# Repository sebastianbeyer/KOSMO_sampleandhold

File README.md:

Triple Sample and Hold module based on the [Schmitzbits YASH](https://www.schmitzbits.de/sah.html). 
I changed some values to improve the droop rate, because I want to use it to sample CV and not audio.
If nothing is plugged into the inputs, it will sample white noise (should be 6V p2p, but you might tweak 
the values of resistors because it always depends on the transistor (reverse avalanche noise)

### Videos to show drop rate with different values for the S&H capacitor

https://www.youtube.com/watch?v=smofjtYN6VY

https://www.youtube.com/watch?v=RdAyaS16wt8

https://www.youtube.com/watch?v=JDEQTLfsh5g

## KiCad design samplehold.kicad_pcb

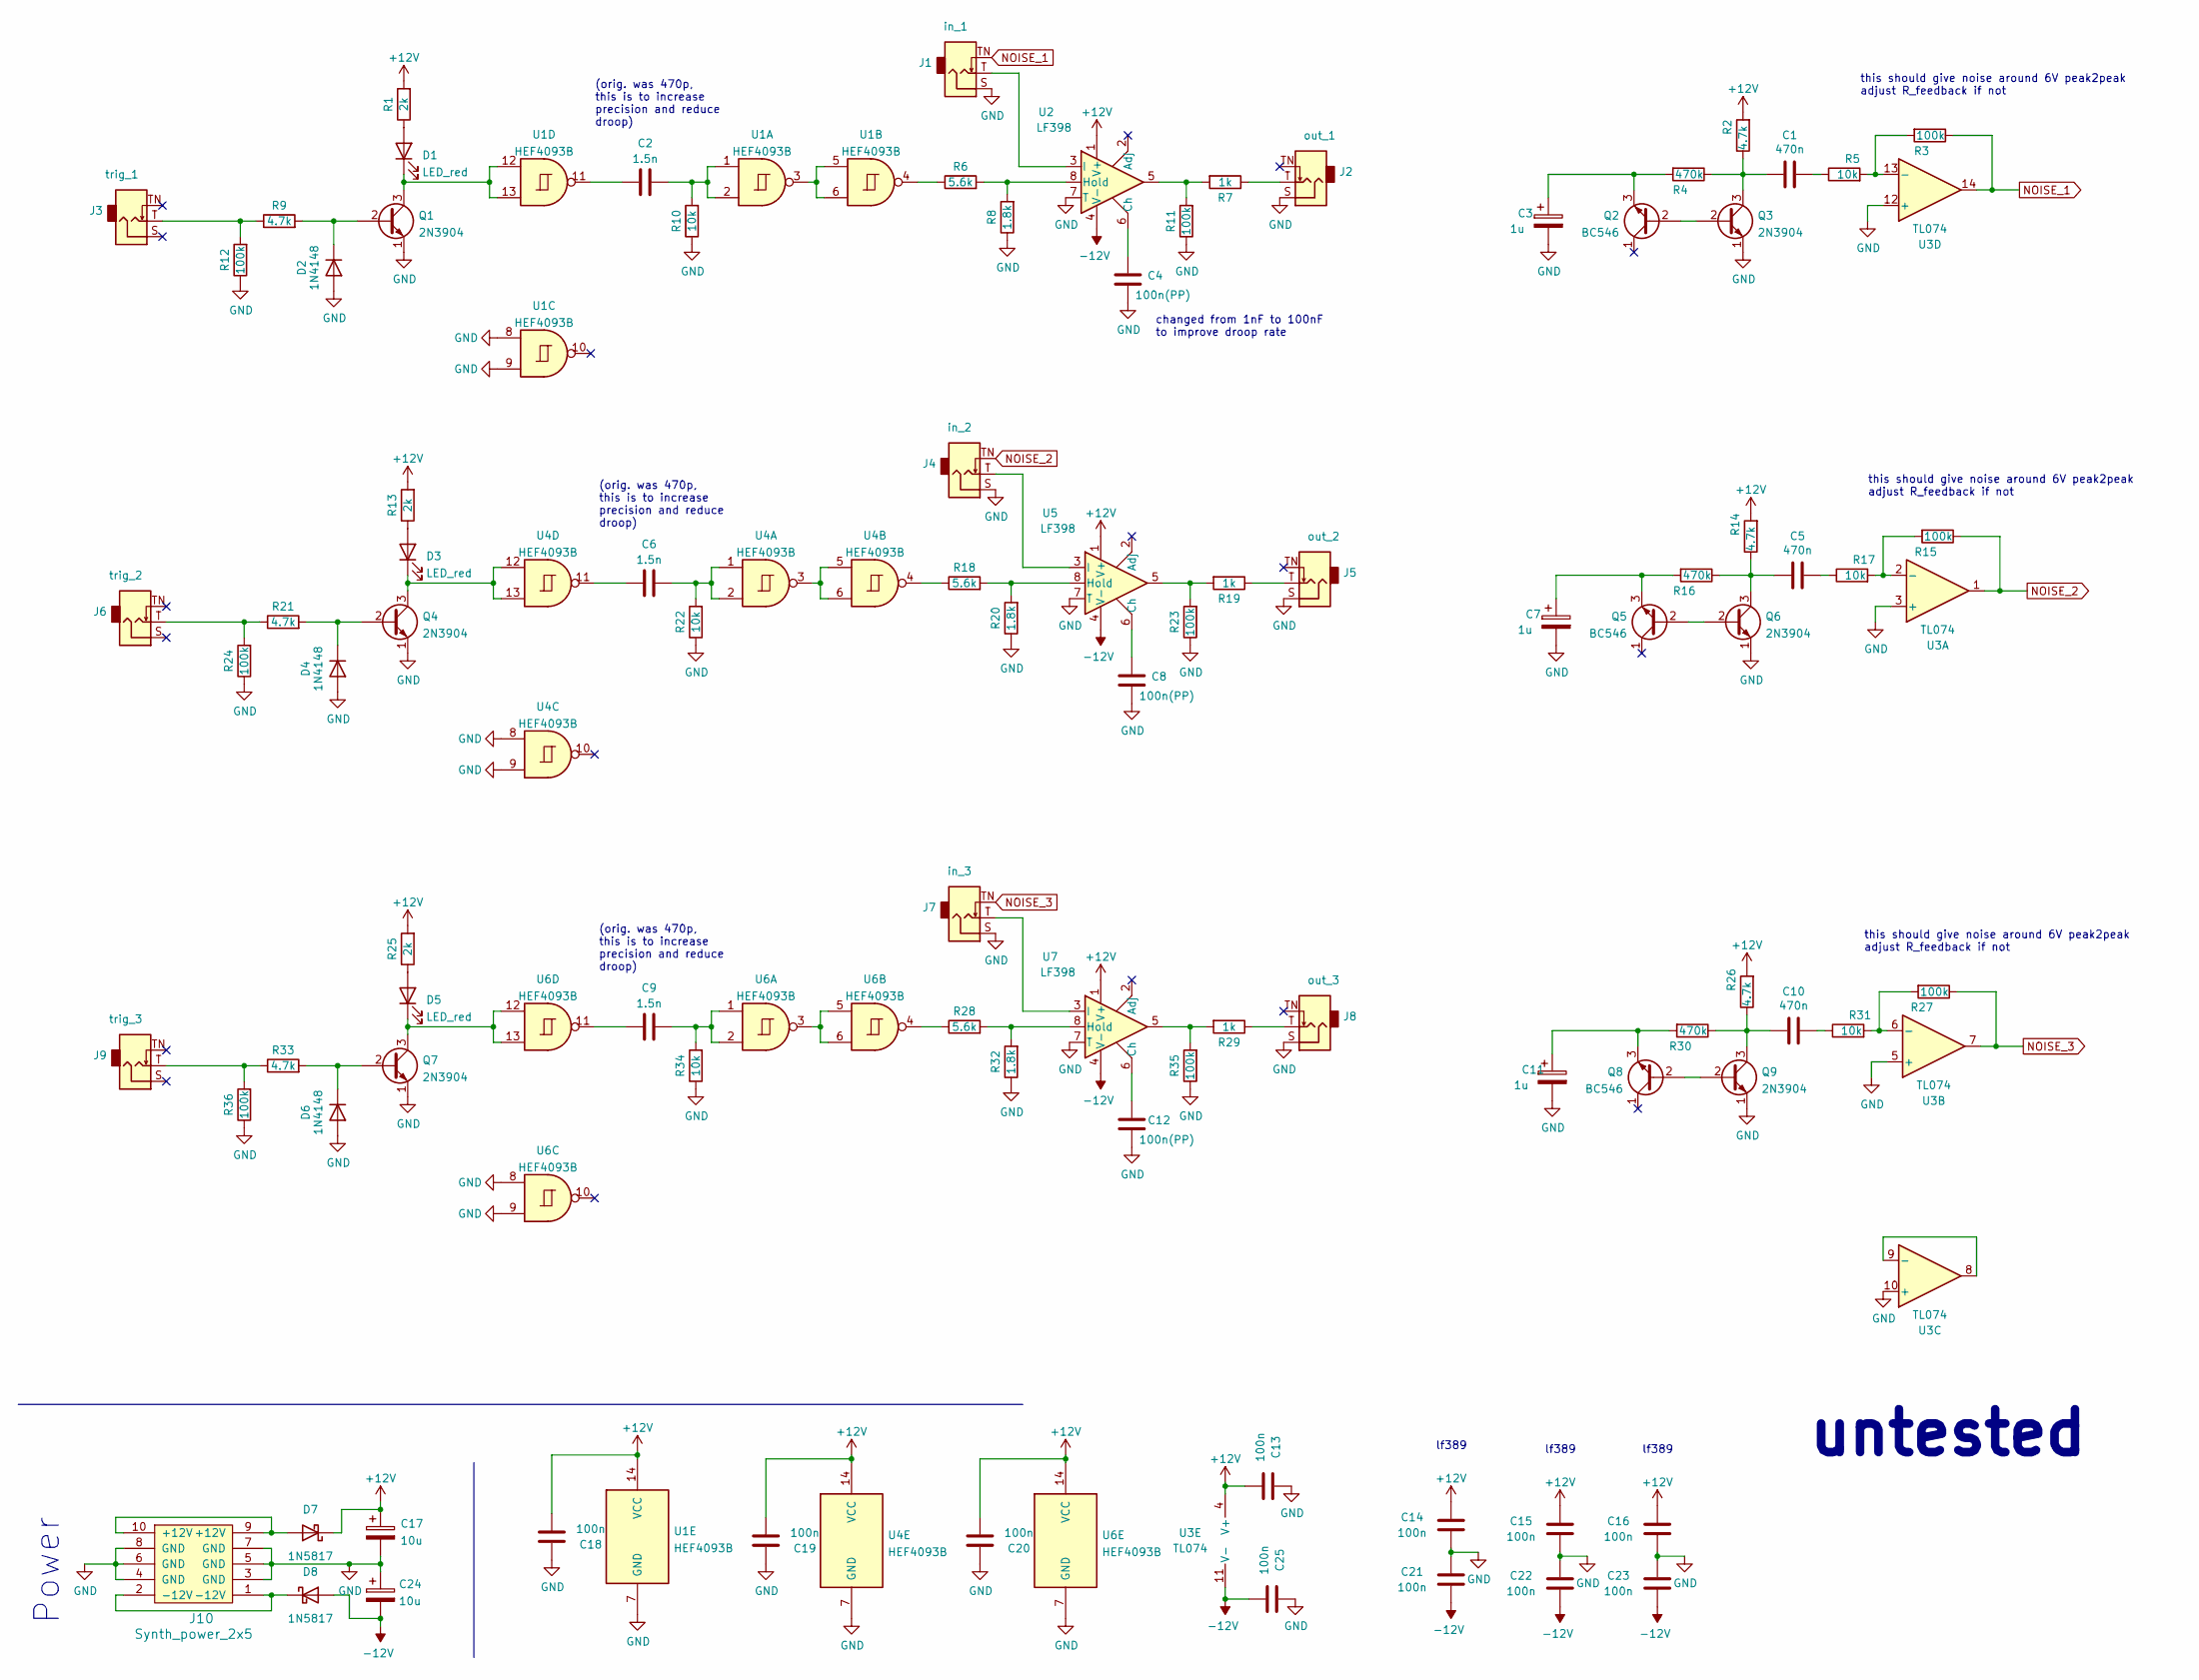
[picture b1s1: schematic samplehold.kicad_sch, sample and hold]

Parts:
C1, C5, C10: 470n; C_Rect_L7.2mm_W2.5mm_P5.00mm_FKS2_FKP2_MKS2_MKP2
C2, C6, C9: 1.5n; C_Rect_L7.2mm_W2.5mm_P5.00mm_FKS2_FKP2_MKS2_MKP2
C3, C7, C11: 1u; CP_Radial_D5.0mm_P2.00mm
C4, C8, C12: 100n(PP); C_Rect_L7.2mm_W2.5mm_P5.00mm_FKS2_FKP2_MKS2_MKP2
C13, C14, C15, C16, C18, C19, C20, C21, C22, C23, C25: 100n; C_Disc_D3.0mm_W1.6mm_P2.50mm
C17, C24: 10u; CP_Radial_D6.3mm_P2.50mm
D1, D3, D5: LED_red; LED_D5.0mm
D2, D4, D6: 1N4148; D_DO-35_SOD27_P7.62mm_Horizontal
D7, D8: 1N5817; D_DO-41_SOD81_P7.62mm_Horizontal
J1: in_1; Jack_6.35mm_PJ_629HAN
J2: out_1; Jack_6.35mm_PJ_629HAN
J3: trig_1; Jack_6.35mm_PJ_629HAN
J4: in_2; Jack_6.35mm_PJ_629HAN
J5: out_2; Jack_6.35mm_PJ_629HAN
J6: trig_2; Jack_6.35mm_PJ_629HAN
J7: in_3; Jack_6.35mm_PJ_629HAN
J8: out_3; Jack_6.35mm_PJ_629HAN
J9: trig_3; Jack_6.35mm_PJ_629HAN
J10: Synth_power_2x5; Power_Header
Q1, Q3, Q4, Q6, Q7, Q9: 2N3904; TO-92_Inline_Wide
Q2, Q5, Q8: BC546; TO-92_Inline_Wide
R1, R13, R25: 2k; R_Axial_DIN0207_L6.3mm_D2.5mm_P2.54mm_Vertical
R2, R9, R14, R21, R26, R33: 4.7k; R_Axial_DIN0207_L6.3mm_D2.5mm_P2.54mm_Vertical
R3, R11, R12, R15, R23, R24, R27, R35, R36: 100k; R_Axial_DIN0207_L6.3mm_D2.5mm_P2.54mm_Vertical
R4, R16, R30: 470k; R_Axial_DIN0207_L6.3mm_D2.5mm_P2.54mm_Vertical
R5, R10, R17, R22, R31, R34: 10k; R_Axial_DIN0207_L6.3mm_D2.5mm_P2.54mm_Vertical
R6, R18, R28: 5.6k; R_Axial_DIN0207_L6.3mm_D2.5mm_P2.54mm_Vertical
R7, R19, R29: 1k; R_Axial_DIN0207_L6.3mm_D2.5mm_P2.54mm_Vertical
R8, R20, R32: 1.8k; R_Axial_DIN0207_L6.3mm_D2.5mm_P2.54mm_Vertical
U1, U4, U6: HEF4093B; DIP-14_W7.62mm_Socket_LongPads
U2, U5, U7: LF398; DIP-8_W7.62mm_Socket_LongPads
U3: TL074; DIP-14_W7.62mm_Socket_LongPads

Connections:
+12V: C13.2, C14.1, C15.1, C16.1, C17.1, C18.2, C19.2, C20.2, D7.1 (K), R1.2, R2.2, R13.2, R14.2, R25.2, R26.2, U1.14 (VCC), U2.1 (V+), U3.4 (V+), U4.14 (VCC), U5.1 (V+), U6.14 (VCC), U7.1 (V+)
-12V: C21.2, C22.2, C23.2, C24.2, C25.2, D8.2 (A), U2.4 (V-), U3.11 (V-), U5.4 (V-), U7.4 (V-)
GND: C3.2, C4.1, C7.2, C8.1, C11.2, C12.1, C13.1, C14.2, C15.2, C16.2, C17.2, C18.1, C19.1, C20.1, C21.1, C22.1, C23.1, C24.1, C25.1, D2.2 (A), D4.2 (A), D6.2 (A), J1.S, J2.S, J4.S, J5.S, J7.S, J8.S, J10.3 (GND), J10.4 (GND), J10.5 (GND), J10.6 (GND), J10.7 (GND), J10.8 (GND), Q1.1 (E), Q3.1 (E), Q4.1 (E), Q6.1 (E), Q7.1 (E), Q9.1 (E), R8.1, R10.1, R11.1, R12.1, R20.1, R22.1, R23.1, R24.1, R32.1, R34.1, R35.1, R36.1, U1.7 (GND), U1.8, U1.9, U2.7 (T), U3.3 (+), U3.5 (+), U3.10 (+), U3.12 (+), U4.7 (GND), U4.8, U4.9, U5.7 (T), U6.7 (GND), U6.8, U6.9, U7.7 (T)
NOISE_1: J1.TN, R3.1, U3.14
NOISE_2: J4.TN, R15.1, U3.1
NOISE_3: J7.TN, R27.1, U3.7
unnamed: C1.1, R5.1
unnamed: C1.2, Q3.3 (C), R2.1, R4.1
unnamed: C2.1, R10.2, U1.1, U1.2
unnamed: C2.2, U1.11
unnamed: C3.1, Q2.3 (E), R4.2
unnamed: C4.2, U2.6 (Ch)
unnamed: C5.1, R17.1
unnamed: C5.2, Q6.3 (C), R14.1, R16.1
unnamed: C6.1, R22.2, U4.1, U4.2
unnamed: C6.2, U4.11
unnamed: C7.1, Q5.3 (E), R16.2
unnamed: C8.2, U5.6 (Ch)
unnamed: C9.1, R34.2, U6.1, U6.2
unnamed: C9.2, U6.11
unnamed: C10.1, R31.1
unnamed: C10.2, Q9.3 (C), R26.1, R30.1
unnamed: C11.1, Q8.3 (E), R30.2
unnamed: C12.2, U7.6 (Ch)
unnamed: D1.1 (K), Q1.3 (C), U1.12, U1.13
unnamed: D1.2 (A), R1.1
unnamed: D2.1 (K), Q1.2 (B), R9.2
unnamed: D3.1 (K), Q4.3 (C), U4.12, U4.13
unnamed: D3.2 (A), R13.1
unnamed: D4.1 (K), Q4.2 (B), R21.2
unnamed: D5.1 (K), Q7.3 (C), U6.12, U6.13
unnamed: D5.2 (A), R25.1
unnamed: D6.1 (K), Q7.2 (B), R33.2
unnamed: D7.2 (A), J10.9 (+12V), J10.10 (+12V)
unnamed: D8.1 (K), J10.1 (-12V), J10.2 (-12V)
unnamed: J1.T, U2.3 (I)
unnamed: J2.T, R7.1
unnamed: J3.T, R9.1, R12.2
unnamed: J4.T, U5.3 (I)
unnamed: J5.T, R19.1
unnamed: J6.T, R21.1, R24.2
unnamed: J7.T, U7.3 (I)
unnamed: J8.T, R29.1
unnamed: J9.T, R33.1, R36.2
unnamed: Q2.2 (B), Q3.2 (B)
unnamed: Q5.2 (B), Q6.2 (B)
unnamed: Q8.2 (B), Q9.2 (B)
unnamed: R3.2, R5.2, U3.13 (-)
unnamed: R6.1, U1.4
unnamed: R6.2, R8.2, U2.8 (Hold)
unnamed: R7.2, R11.2, U2.5
unnamed: R15.2, R17.2, U3.2 (-)
unnamed: R18.1, U4.4
unnamed: R18.2, R20.2, U5.8 (Hold)
unnamed: R19.2, R23.2, U5.5
unnamed: R27.2, R31.2, U3.6 (-)
unnamed: R28.1, U6.4
unnamed: R28.2, R32.2, U7.8 (Hold)
unnamed: R29.2, R35.2, U7.5
unnamed: U1.3, U1.5, U1.6
unnamed: U3.8, U3.9 (-)
unnamed: U4.3, U4.5, U4.6
unnamed: U6.3, U6.5, U6.6

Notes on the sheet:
this should give noise around 6V peak2peak adjust R_feedback if not
untested
lf389
changed from 1nF to 100nF to improve droop rate
Power
(orig. was 470p, this is to increase precision and reduce droop)

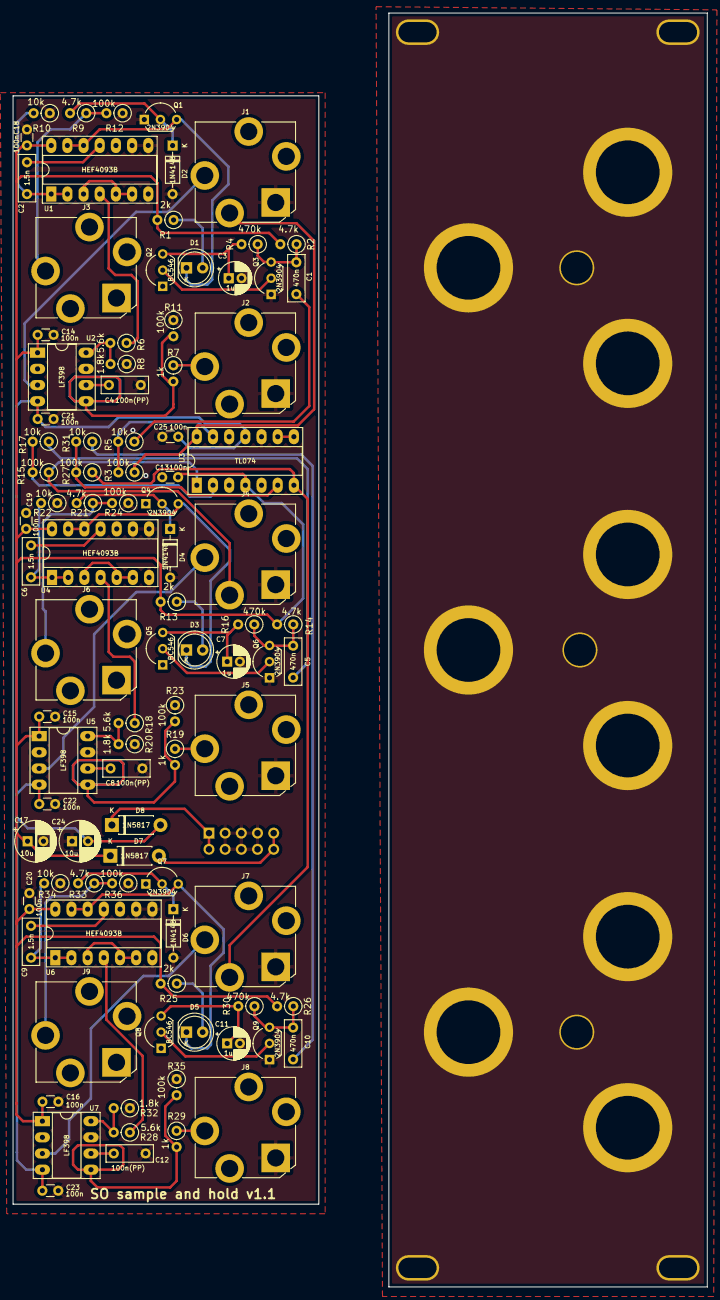
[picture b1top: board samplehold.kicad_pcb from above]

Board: 2 copper layers, 109.0 x 200.0 mm, 95 parts (1 on the bottom side), 63 nets.

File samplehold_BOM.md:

# samplehold.kicad_sch BOM

Tue 13 Dec 2022 10:51:27 CET

Generated from schematic by Eeschema 6.0.8-f2edbf62ab~116~ubuntu22.04.1

**Component Count:** 95

| Refs | Qty | Component | Description | Vendor | SKU |
| ----- | --- | ---- | ----------- | ---- | ---- |
| C1, C5, C10 | 3 | 470n | Unpolarized capacitor | Tayda |  |
| C2, C6, C9 | 3 | 1.5n | Unpolarized capacitor |  |  |
| C3, C7, C11 | 3 | 1u | Polarized capacitor | Tayda |  |
| C4, C8, C12 | 3 | 100n(PP) | Unpolarized capacitor |  |  |
| C13, C14, C15, C16, C18, C19, C20, C21, C22, C23, C25 | 11 | 100n | Unpolarized capacitor |  |  |
| C17, C24 | 2 | 10u | Polarized capacitor | Tayda |  |
| D1, D3, D5 | 3 | LED_red | Light emitting diode | Tayda | A-1554 |
| D2, D4, D6 | 3 | 1N4148 | Standard switching diode, DO-35 | Tayda | A-157 |
| D7, D8 | 2 | 1N5817 | Schottky Barrier Rectifier Diode, DO-41 | Tayda | A-159 |
| J1 | 1 | in_1 | Audio Jack, 2 Poles (Mono / TS), Switched T Pole (Normalling) | Tayda | A-1121 |
| J2 | 1 | out_1 | Audio Jack, 2 Poles (Mono / TS), Switched T Pole (Normalling) | Tayda | A-1121 |
| J3 | 1 | trig_1 | Audio Jack, 2 Poles (Mono / TS), Switched T Pole (Normalling) | Tayda | A-1121 |
| J4 | 1 | in_2 | Audio Jack, 2 Poles (Mono / TS), Switched T Pole (Normalling) | Tayda | A-1121 |
| J5 | 1 | out_2 | Audio Jack, 2 Poles (Mono / TS), Switched T Pole (Normalling) | Tayda | A-1121 |
| J6 | 1 | trig_2 | Audio Jack, 2 Poles (Mono / TS), Switched T Pole (Normalling) | Tayda | A-1121 |
| J7 | 1 | in_3 | Audio Jack, 2 Poles (Mono / TS), Switched T Pole (Normalling) | Tayda | A-1121 |
| J8 | 1 | out_3 | Audio Jack, 2 Poles (Mono / TS), Switched T Pole (Normalling) | Tayda | A-1121 |
| J9 | 1 | trig_3 | Audio Jack, 2 Poles (Mono / TS), Switched T Pole (Normalling) | Tayda | A-1121 |
| J10 | 1 | Synth_power_2x5 | Pin header 2.54 mm 2x5 | Tayda | A-2939 |
| Q1, Q3, Q4, Q6, Q7, Q9 | 6 | 2N3904 | Small Signal NPN Transistor, TO-92 | Tayda | A-111 |
| Q2, Q5, Q8 | 3 | BC546 | 0.1A Ic, 65V Vce, Small Signal NPN Transistor, TO-92 |  |  |
| R1, R13, R25 | 3 | 2k | Resistor | Tayda |  |
| R2, R9, R14, R21, R26, R33 | 6 | 4.7k | Resistor | Tayda |  |
| R3, R11, R12, R15, R23, R24, R27, R35, R36 | 9 | 100k | Resistor | Tayda |  |
| R4, R16, R30 | 3 | 470k | Resistor | Tayda |  |
| R5, R10, R17, R22, R31, R34 | 6 | 10k | Resistor | Tayda |  |
| R6, R18, R28 | 3 | 5.6k | Resistor | Tayda |  |
| R7, R19, R29 | 3 | 1k | Resistor | Tayda |  |
| R8, R20, R32 | 3 | 1.8k | Resistor | Tayda |  |
| U1, U4, U6 | 3 | HEF4093B | Quad 2-Input NAND Schmitt Trigger, SOIC-14 |  |  |
| U2, U5, U7 | 3 | LF398 | Sample And Hold Unity Gain Follower, DIP-8 |  |  |
| U3 | 1 | TL074 | Quad operational amplifier, DIP-14 | Tayda | A-1138 |

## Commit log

2022-12-13 update to 1.1 with 100nF caps instead of 1nF
2022-12-13 add readme
